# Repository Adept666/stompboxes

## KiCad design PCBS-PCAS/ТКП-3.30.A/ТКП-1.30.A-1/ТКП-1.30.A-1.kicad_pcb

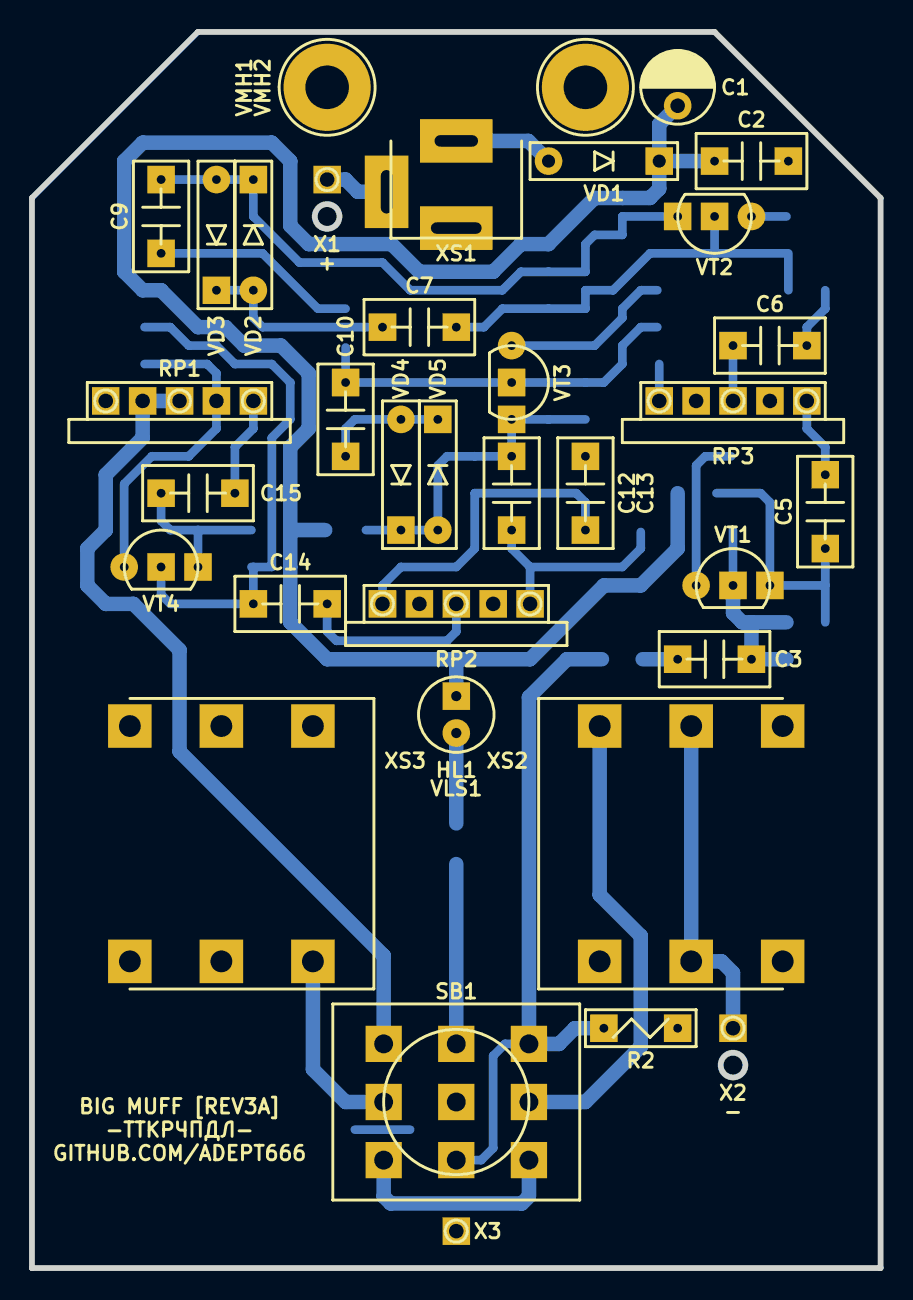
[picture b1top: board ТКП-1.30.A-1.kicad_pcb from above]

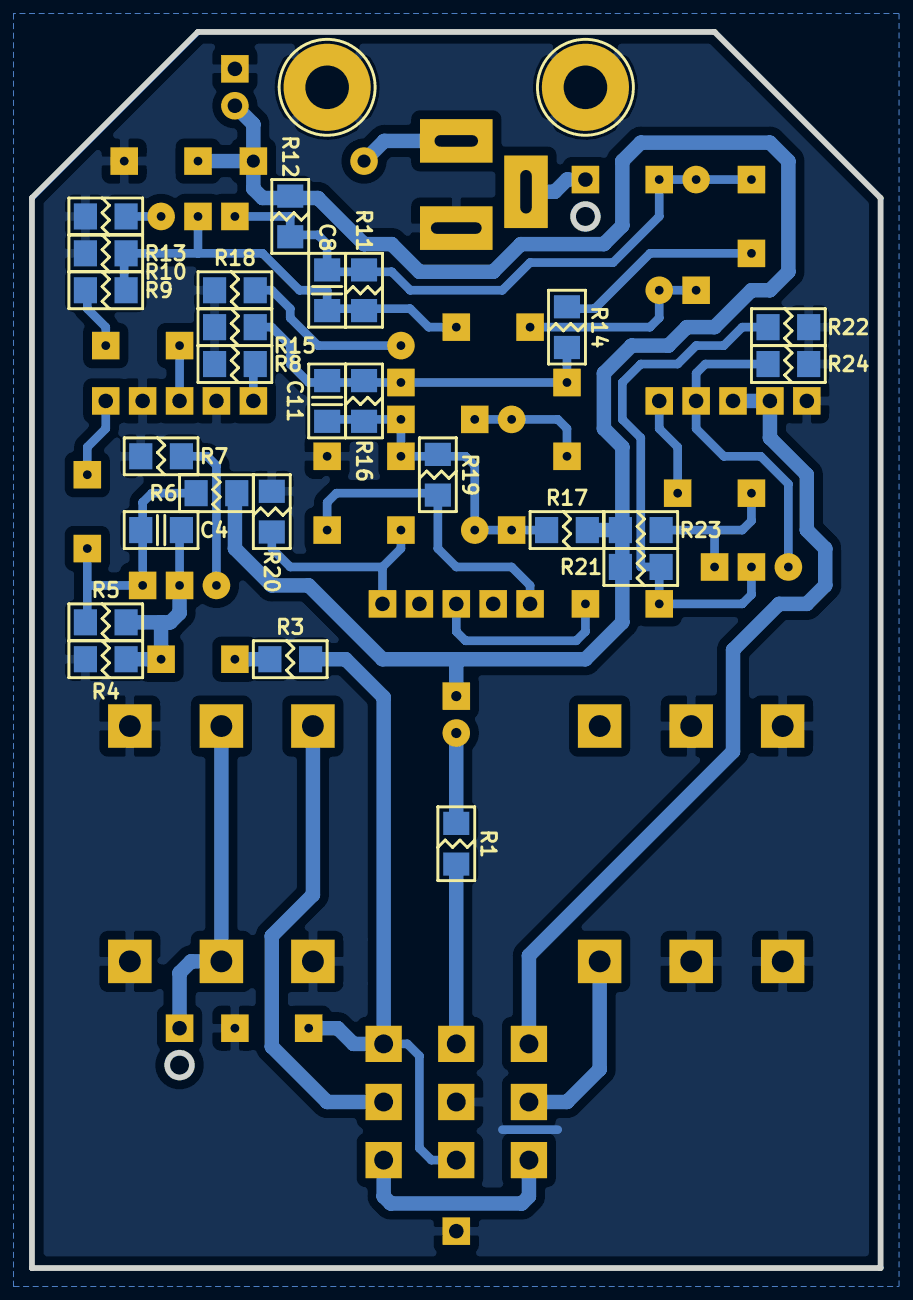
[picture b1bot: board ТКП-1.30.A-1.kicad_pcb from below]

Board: 2 copper layers, 58.4 x 85.1 mm, 64 parts (26 on the bottom side), 36 nets.

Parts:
C1: 106; CP-RADIAL-D05.0-P02.0-CLS
C2: 104; C-DISK-D04.2-T03.0-P05.08-d0.5
C3, C5, C6, C7, C9, C10, C14, C15: 105; C-DISK-D04.2-T03.0-P05.08-d0.5
C4, C8, C11: 471; C-SM-1206
C12: 392; C-DISK-D04.2-T03.0-P05.08-d0.5
C13: 103; C-DISK-D04.2-T03.0-P05.08-d0.5
GB1: PP3; B-PP3-HV
HL1: FYL-5013UWC; LED-ROUND-05.0-UNI-SH-SPACER-PNL-5.3
R1, R6, R9, R12, R14, R17, R23: 103; R-SM-1206
R2: 105; R-MFR-12
R3: 393; R-SM-1206
R4, R10, R15, R22: 104; R-SM-1206
R5: 514; R-SM-1206
R7: 101; R-SM-1206
R8: 182; R-SM-1206
R11, R16, R21: 474; R-SM-1206
R13, R18: 391; R-SM-1206
R19, R20: 223; R-SM-1206
R24: 202; R-SM-1206
RP1, RP3: A100K; RPB-18-1x17-1.6-PNL-7.4-2.8
RP2: B100K; RPB-18-1x17-1.6-PNL-7.4-2.8
SB1: PBS-24-302SP; SW-PBS-24-302SP-2.5-PNL-13.0
VD1: 5817; P-DO-41
VD2, VD3, VD4, VD5: 6263; P-DO-35
VE1: B013; B013_E1
VLS1: BR-12.7; VLS-BR
VMH1, VMH2: DI5M3x18; VMH-STA-DA5-PNL-3.0
VT1, VT2, VT3, VT4: 5088; P-TO-92-E-B-C
X1: +; CON-PAD-S-1.0-1.9
X2: -; CON-PAD-S-1.0-1.9
X3: COM; CON-PAD-S-1.0-1.9
XS1: DC-005; CON-DC-005
XS2, XS3: PJ-644C; CON-PJ-644C

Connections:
/IN-CIR: R2.2, R3.1, SB1.NC2, SB1.NO3
/IN-CON: SB1.COM3, XS2.T
/LED: R1.1, SB1.NO2
/OUT-CIR: RP1.2, RP1.NC1, SB1.NO1
/OUT-CON: SB1.COM1, XS3.T
/PP3-NEG: X2.1, XS2.R, XS2.RN
/PP3-POS: X1.1, XS1.SN
COM: C1.-, C2.2, C13.2, R2.1, R4.1, R7.1, R8.1, R10.1, R13.1, R15.1, R18.1, R20.2, R22.1, R24.1, RP1.1, RP3.NC1, RP3.NC2, SB1.COM2, VMH1.0, VMH2.0, X3.1, XS1.C, XS2.S, XS2.SN, XS2.TN, XS3.R, XS3.RN, XS3.S, XS3.SN
unnamed: C3.1, R3.2
unnamed: C3.2, C4.1, R4.2, R5.1, VT1.B
unnamed: C4.2, C5.1, R5.2, R6.1, VT1.C
unnamed: C5.2, RP3.3
unnamed: C6.1, RP3.2
unnamed: C6.2, R9.1
unnamed: C7.1, C8.1, R9.2, R10.2, R11.1, VT2.B
unnamed: C7.2, VD2.A, VD3.C
unnamed: C8.2, C9.1, R11.2, R12.1, VD2.C, VD3.A, VT2.C
unnamed: C9.2, R14.1
unnamed: C10.1, C11.1, R14.2, R15.2, R16.1, VT3.B
unnamed: C10.2, VD4.A, VD5.C
unnamed: C11.2, C12.1, R16.2, R17.1, R19.1, VD4.C, VD5.A, VT3.C
unnamed: C12.2, R20.1, RP2.3
unnamed: C13.1, R19.2, RP2.1
unnamed: C14.1, RP2.2
unnamed: C14.2, R21.1, R22.2, VT4.B
unnamed: C15.1, R23.1, VT4.C
unnamed: C15.2, RP1.3
unnamed: HL1.C, R1.2
unnamed: R7.2, VT1.E
unnamed: R8.2, RP3.1
unnamed: R13.2, VT2.E
unnamed: R18.2, VT3.E
unnamed: R24.2, RP1.NC2, VT4.E
unnamed: SB1.NC1, SB1.NC3
unnamed: VD1.A, XS1.S
V: C1.+, C2.1, HL1.A, R6.2, R12.2, R17.2, R21.2, R23.2, VD1.C

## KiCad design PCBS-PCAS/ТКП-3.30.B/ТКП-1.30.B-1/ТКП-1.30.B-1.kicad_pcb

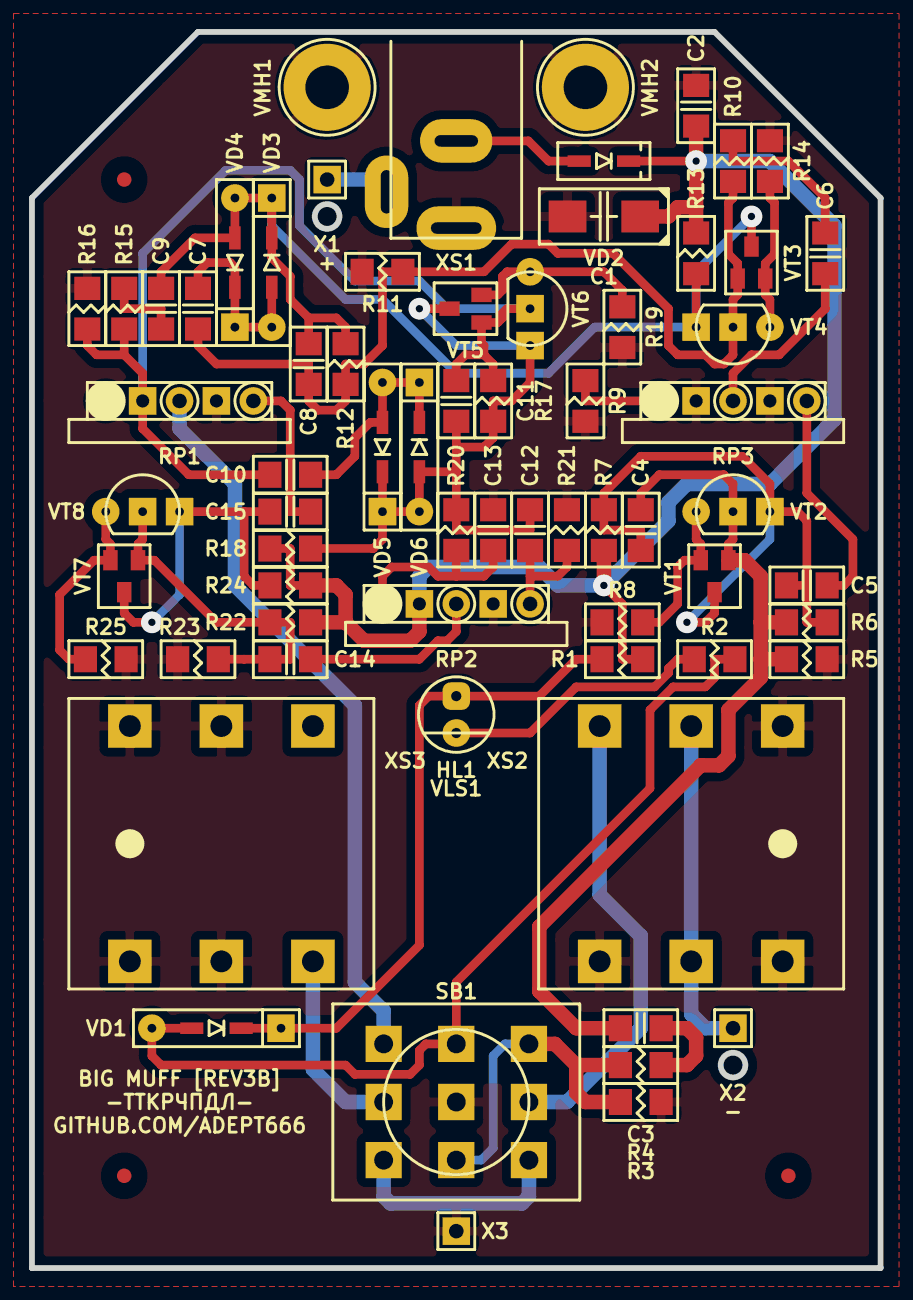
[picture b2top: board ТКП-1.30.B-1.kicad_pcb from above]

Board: 2 copper layers, 58.4 x 85.1 mm, 73 parts (0 on the bottom side), 37 nets.

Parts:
C1: 106; CP-CTSMD-C
C2: 104; C-SM-1206
C3, C5, C6, C7, C9, C10, C14, C15: 105; C-SM-1206
C4, C8, C11: 471; C-SM-1206
C12: 392; C-SM-1206
C13: 103; C-SM-1206
GB1: PP3; B-PP3-HV
HL1: FYL-5013UWC; LED-ROUND-05.0-UNI-SH-SPACER-PNL-5.3
R1: 0; R-SM-1206
R2, R7, R10, R13, R15, R18, R24: 103; R-SM-1206
R3: 105; R-SM-1206
R4: 393; R-SM-1206
R5, R11, R16, R23: 104; R-SM-1206
R6: 514; R-SM-1206
R8: 101; R-SM-1206
R9: 182; R-SM-1206
R12, R17, R22: 474; R-SM-1206
R14, R19: 391; R-SM-1206
R20, R21: 223; R-SM-1206
R25: 202; R-SM-1206
RP1, RP3: A100K; RPB-18-1x17-1.6-PNL-7.4-2.8
RP2: B100K; RPB-18-1x17-1.6-PNL-7.4-2.8
SB1: PBS-24-302SP; SW-PBS-24-302SP-2.5-PNL-13.0
VD1: X; P-SOD-123-OR-DO-35-V2
VD2: 0520; P-SOD-123
VD3, VD4, VD5, VD6: 6263; P-SOD-123-OR-DO-35-V2
VE1: B013; B013_E1
VFM1, VFM2, VFM3: 1.0; VFM-1.0-3.0-SL
VLS1: BR-12.7; VLS-BR-P
VMH1, VMH2: DI5M3x18; VMH-STA-DA5-PNL-3.0
VT1, VT3, VT5, VT7: 5088; P-SOT-23-B-E-C
VT2, VT4, VT6, VT8: 5088; P-TO-92-E-B-C
X1: +; CON-PAD-S-1.0-1.9
X2: -; CON-PAD-S-1.0-1.9
X3: COM; CON-PAD-S-1.0-1.9
XS1: DC-005; CON-DC-005-9V-OVAL
XS2, XS3: PJ-644C; CON-PJ-644C-IN-OR-OUT

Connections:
/1B: C3.2, C4.1, R5.2, R6.1, VT1.B, VT2.B
/1C: C4.2, C5.1, R6.2, R7.1, VT1.C, VT2.C
/1E: R8.2, VT1.E, VT2.E
/2B: C7.1, C8.1, R10.2, R11.2, R12.1, VT3.B, VT4.B
/2C: C8.2, C9.1, R12.2, R13.1, VD3.C, VD4.A, VT3.C, VT4.C
/2E: R14.2, VT3.E, VT4.E
/3B: C10.1, C11.1, R15.2, R16.2, R17.1, RP1.NC1, VT5.B, VT6.B
/3C: C11.2, C12.1, R17.2, R18.1, R20.1, VD5.C, VD6.A, VT5.C, VT6.C
/3E: R19.2, VT5.E, VT6.E
/4B: C14.2, R22.1, R23.2, VT7.B, VT8.B
/4C: C15.1, R24.1, VT7.C, VT8.C
/4E: R25.2, VT7.E, VT8.E
/IN-CIR: R3.2, R4.1, SB1.NC2, SB1.NO3
/IN-CON: SB1.COM3, XS2.T
/LED: R2.1, SB1.NO2, VD1.A
/OUT-CIR: RP1.2, SB1.NO1
/OUT-CON: SB1.COM1, XS3.T
/PP3-NEG: X2.1, XS2.R, XS2.RN
/PP3-POS: X1.1, XS1.SN
COM: C1.-, C2.2, C13.2, R3.1, R5.1, R8.1, R9.1, R11.1, R14.1, R16.1, R19.1, R21.2, R23.1, R25.1, RP1.1, RP1.NC2, RP2.NC2, RP3.NC1, RP3.NC2, SB1.COM2, VMH1.0, VMH2.0, X3.1, XS1.C, XS2.S, XS2.SN, XS2.TN, XS3.R, XS3.RN, XS3.S, XS3.SN
unnamed: C3.1, R4.2
unnamed: C5.2, RP3.3
unnamed: C6.1, RP3.2
unnamed: C6.2, R10.1
unnamed: C7.2, VD3.A, VD4.C
unnamed: C9.2, R15.1
unnamed: C10.2, VD5.A, VD6.C
unnamed: C12.2, R21.1, RP2.3
unnamed: C13.1, R20.2, RP2.1
unnamed: C14.1, RP2.2
unnamed: C15.2, RP1.3
unnamed: HL1.A, R1.2, VD1.C
unnamed: HL1.C, R2.2
unnamed: R9.2, RP3.1
unnamed: SB1.NC1, SB1.NC3
unnamed: VD2.A, XS1.S
V: C1.+, C2.1, R1.1, R7.2, R13.2, R18.2, R22.2, R24.2, RP2.NC1, VD2.C

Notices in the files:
PCBS-PCAS/ТКП-3.30.A/ТКП-1.30.A-1/ТКП-1.30.A-1.kicad_pcb:
This project is licensed under GNU General Public License v3.0 or later
